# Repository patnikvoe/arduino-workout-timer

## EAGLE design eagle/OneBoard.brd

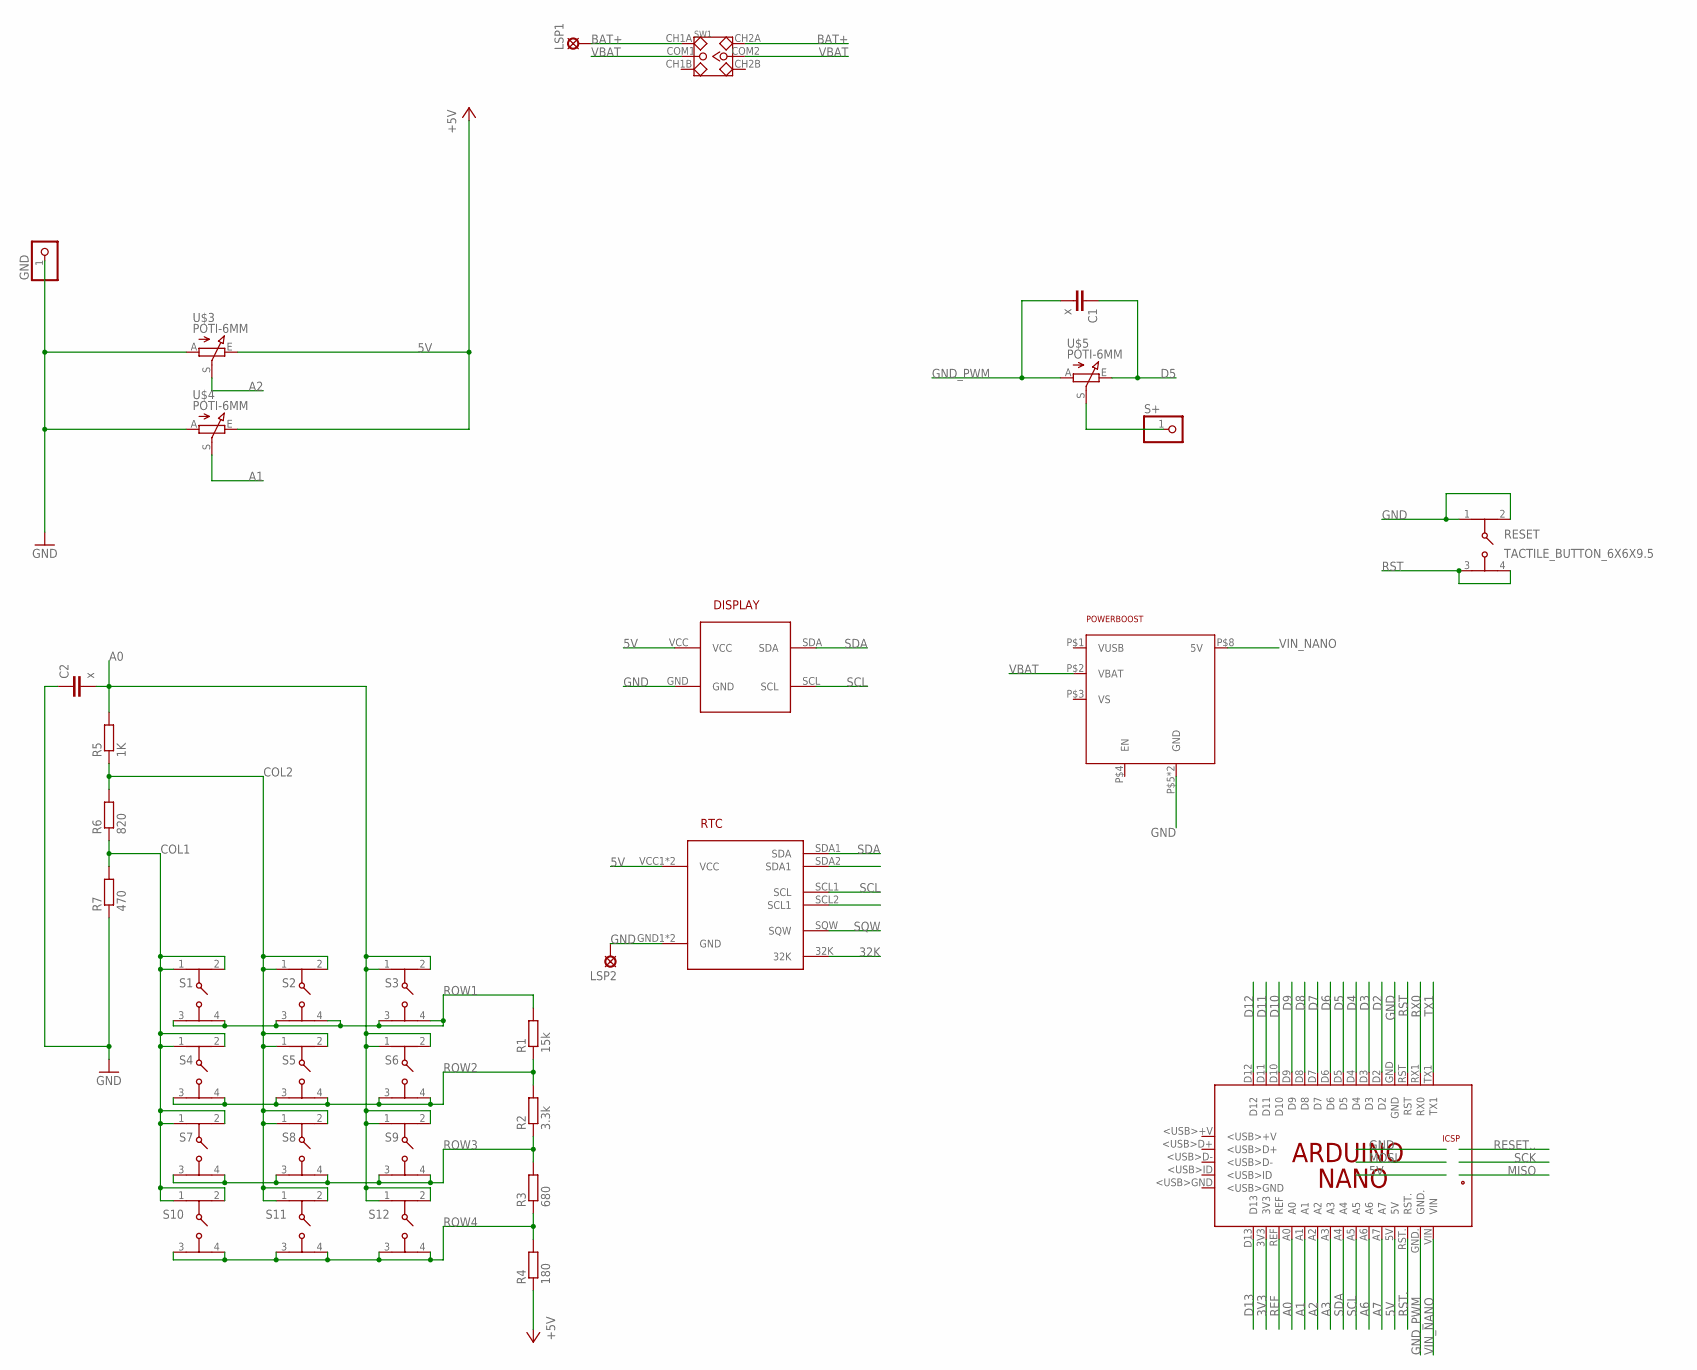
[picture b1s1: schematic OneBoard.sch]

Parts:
C1, C2: x; C025-025X050
DISPLAY: OLED_BREAKOUT; OLED_128X32_BREAKOUT
GND: PINHD-1X1; 1X01
LSP1, LSP2: LSP11
POWERBOOST: ADAFRUIT_POWERBOOST_1000C
R1: 15k; R0603
R2: 3.3k; R0603
R3: 680; R0603
R4: 180; R0603
R5: 1K; R0603
R6: 820; R0603
R7: 470; R0603
RESET: TACTILE_BUTTON_6X6X9.5; TACTILE_SWITCH_PTH_6.0MM
RTC: DS3231_BREAKOUT
S1, S2, S3, S4, S5, S6, S7, S8, S9, S10, S11, S12: TACTILE_BUTTON_6X6X9.5; TACTILE_SWITCH_PTH_6.0MM
S+: PINHD-1X1; 1X01
SW1: DIP-TOGGLE-SWITCH-2CH-(2X3P-2.54); SW6-2.54-9.0X3.5X3.2+2.0MM
U$3, U$4, U$5: POTI-6MM
U$7: ARDUINO-NANO; ARDUINO_NANO

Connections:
3V3: U$7.3V3
5V: DISPLAY.VCC, R4.1, RTC.VCC1 (VCC), RTC.VCC2 (VCC), U$3.E, U$4.E, U$7.5V, U$7.5V.
32K: RTC.32K
A0: C2.2, R5.2, S3.1, S3.2 (3), S6.1, S6.2 (3), S9.1, S9.2 (3), S12.1, S12.2 (3), U$7.A0
A1: U$4.S, U$7.A1
A2: U$3.S, U$7.A2
A3: U$7.A3
A6: U$7.A6
A7: U$7.A7
BAT+: LSP1.MP, SW1.CH1A, SW1.CH2A
COL1: R6.1, R7.2, S1.1, S1.2 (3), S4.1, S4.2 (3), S7.1, S7.2 (3), S10.1, S10.2 (3)
COL2: R5.1, R6.2, S2.1, S2.2 (3), S5.1, S5.2 (3), S8.1, S8.2 (3), S11.1, S11.2 (3)
D2: U$7.D2
D3: U$7.D3
D4: U$7.D4
D5: C1.1, U$5.E, U$7.D5
D6: U$7.D6
D7: U$7.D7
D8: U$7.D8
D9: U$7.D9
D10: U$7.D10
D11: U$7.D11
D12: U$7.D12
D13: U$7.D13
GND: C2.1, DISPLAY.GND, GND.1, LSP2.MP, POWERBOOST.P$5 (GND), POWERBOOST.P$7 (GND), R7.1, RESET.1, RESET.2 (3), RTC.GND1 (GND), RTC.GND2 (GND), U$3.A, U$4.A, U$7.GND, U$7.GND_
GND_PWM: C1.2, U$5.A, U$7.GND.
MISO: U$7.MISO
MOSI: U$7.MOSI
REF: U$7.REF
RESET..: U$7.RESET..
ROW1: R1.2, S1.3 (2), S1.4, S2.3 (2), S2.4, S3.3 (2), S3.4
ROW2: R1.1, R2.2, S4.3 (2), S4.4, S5.3 (2), S5.4, S6.3 (2), S6.4
ROW3: R2.1, R3.2, S7.3 (2), S7.4, S8.3 (2), S8.4, S9.3 (2), S9.4
ROW4: R3.1, R4.2, S10.3 (2), S10.4, S11.3 (2), S11.4, S12.3 (2), S12.4
RST: RESET.3 (2), RESET.4, U$7.RST
RST.: U$7.RST.
RX0: U$7.RX1 (RX0)
S+: S+.1, U$5.S
SCK: U$7.SCK
SCL: DISPLAY.SCL, RTC.SCL1 (SCL), U$7.A5
SDA: DISPLAY.SDA, RTC.SDA1 (SDA), U$7.A4
SQW: RTC.SQW
TX1: U$7.TX1
VBAT: POWERBOOST.P$2 (VBAT), SW1.COM1, SW1.COM2
VIN_NANO: POWERBOOST.P$8 (5V), U$7.VIN
VS: POWERBOOST.P$3 (VS)
VUSB: POWERBOOST.P$1 (VUSB)

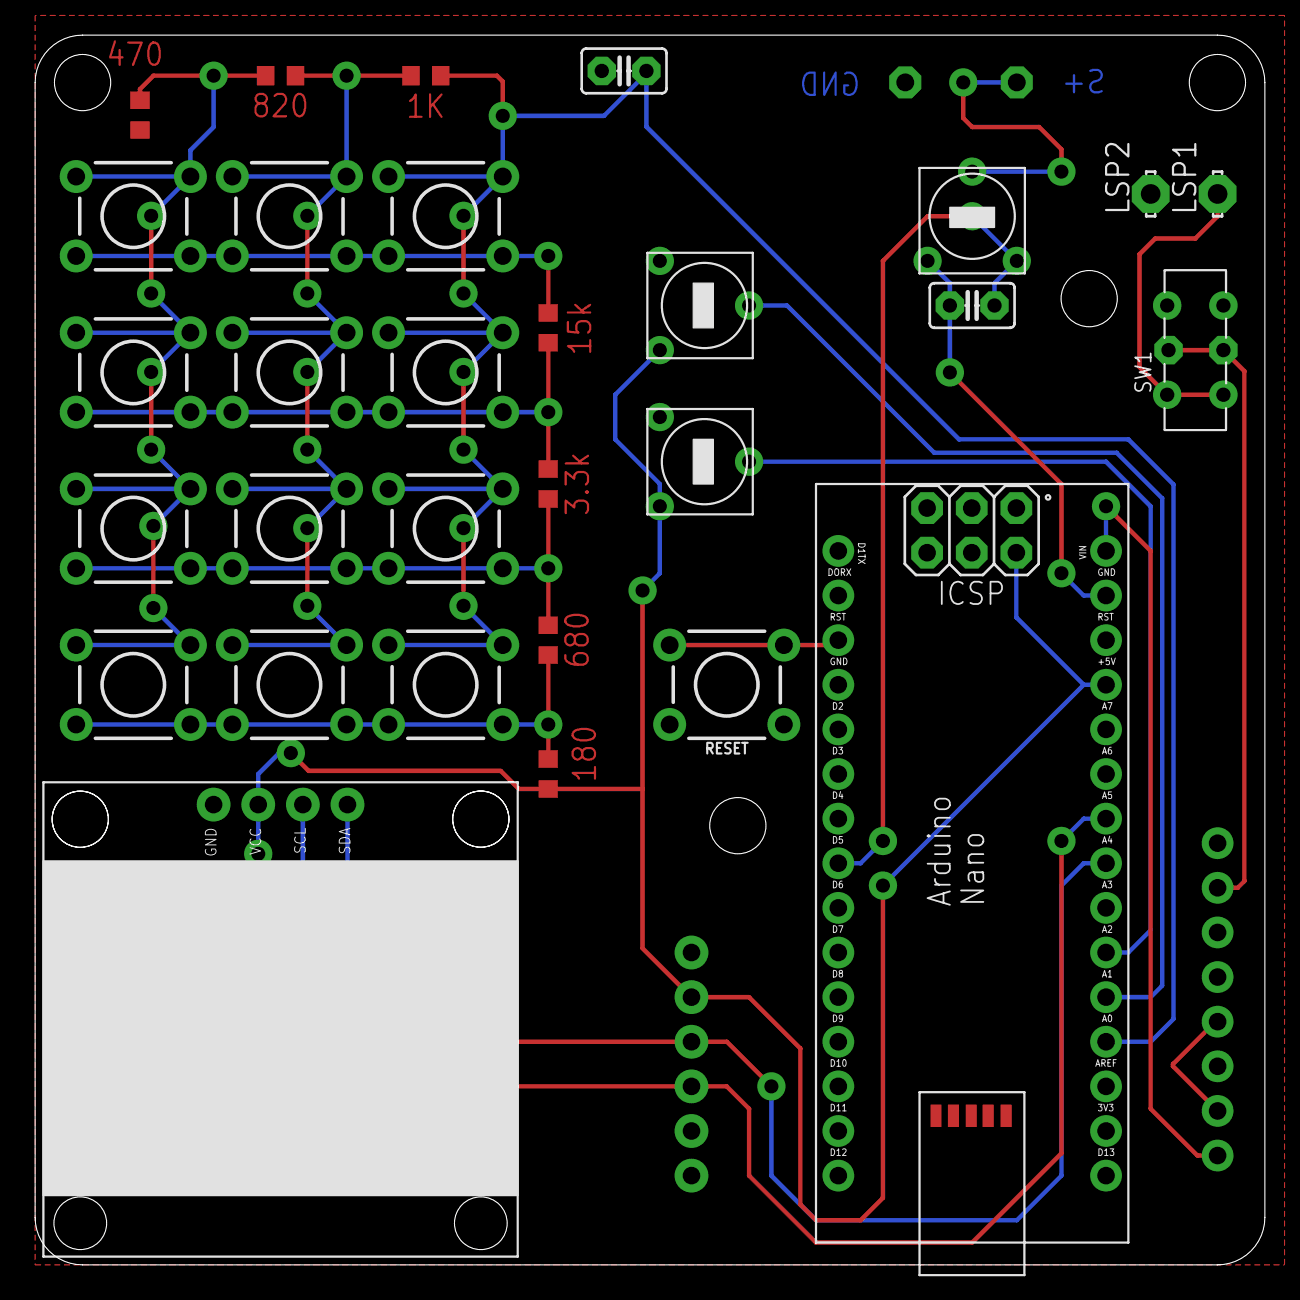
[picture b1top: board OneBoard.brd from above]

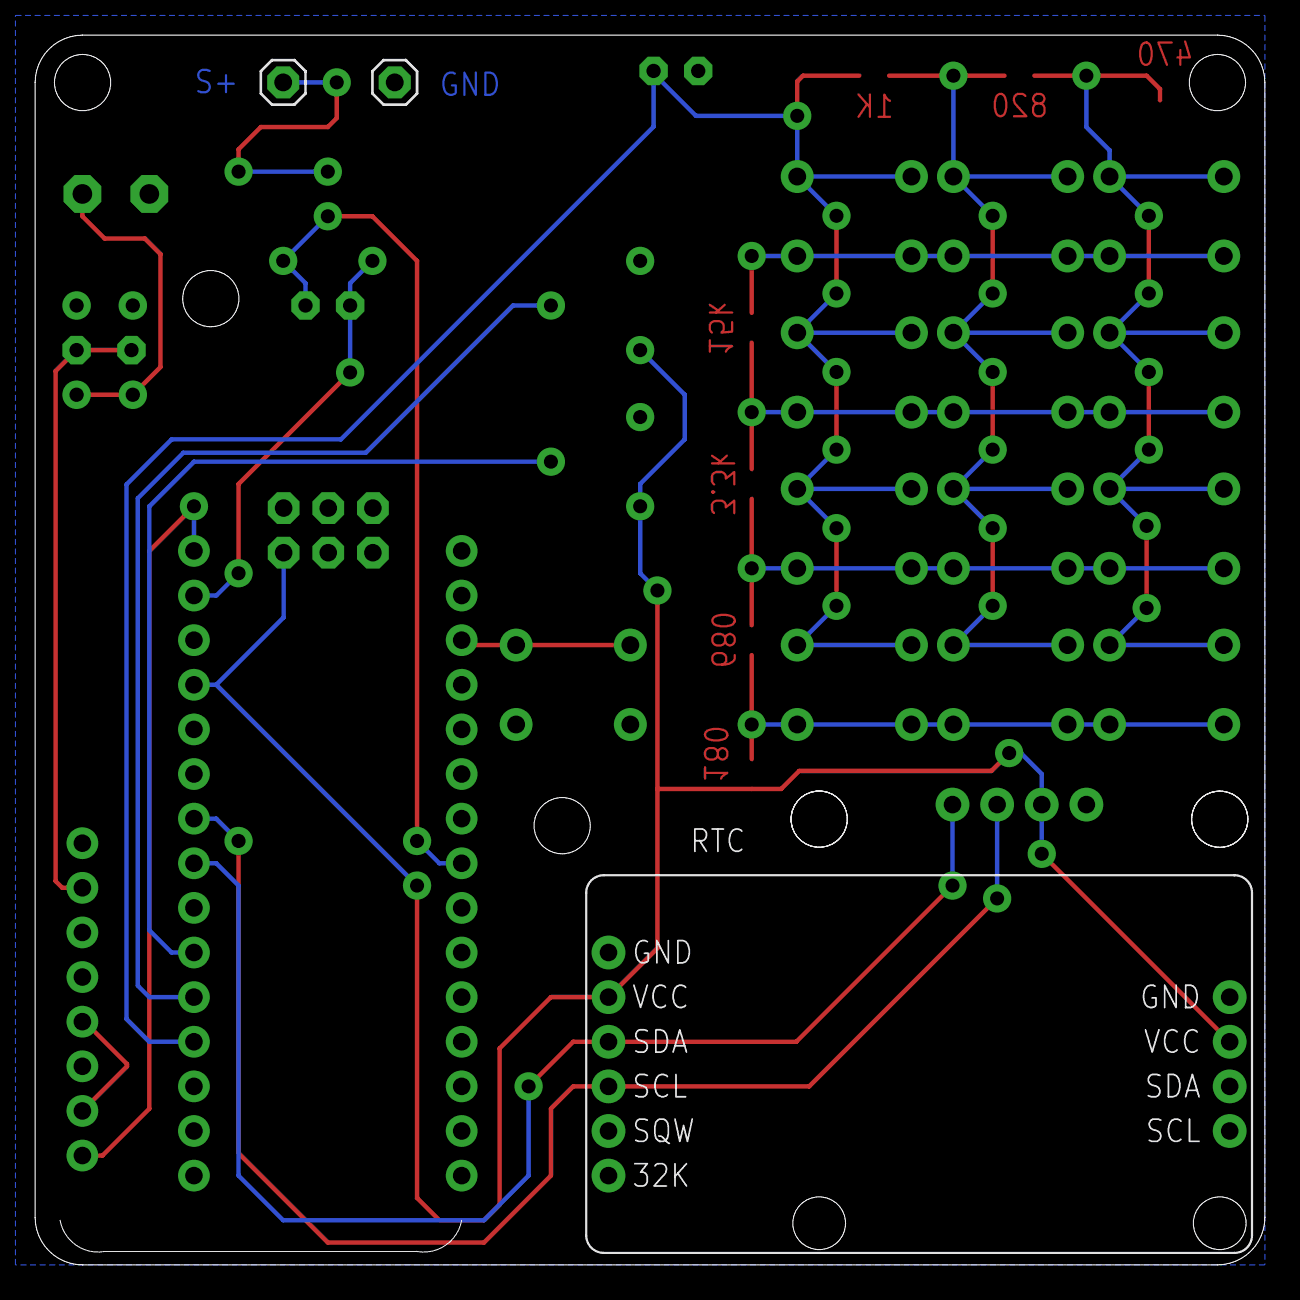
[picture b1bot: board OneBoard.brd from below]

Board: 2 copper layers, 70.0 x 70.0 mm, 34 parts (4 on the bottom side), 20 nets.

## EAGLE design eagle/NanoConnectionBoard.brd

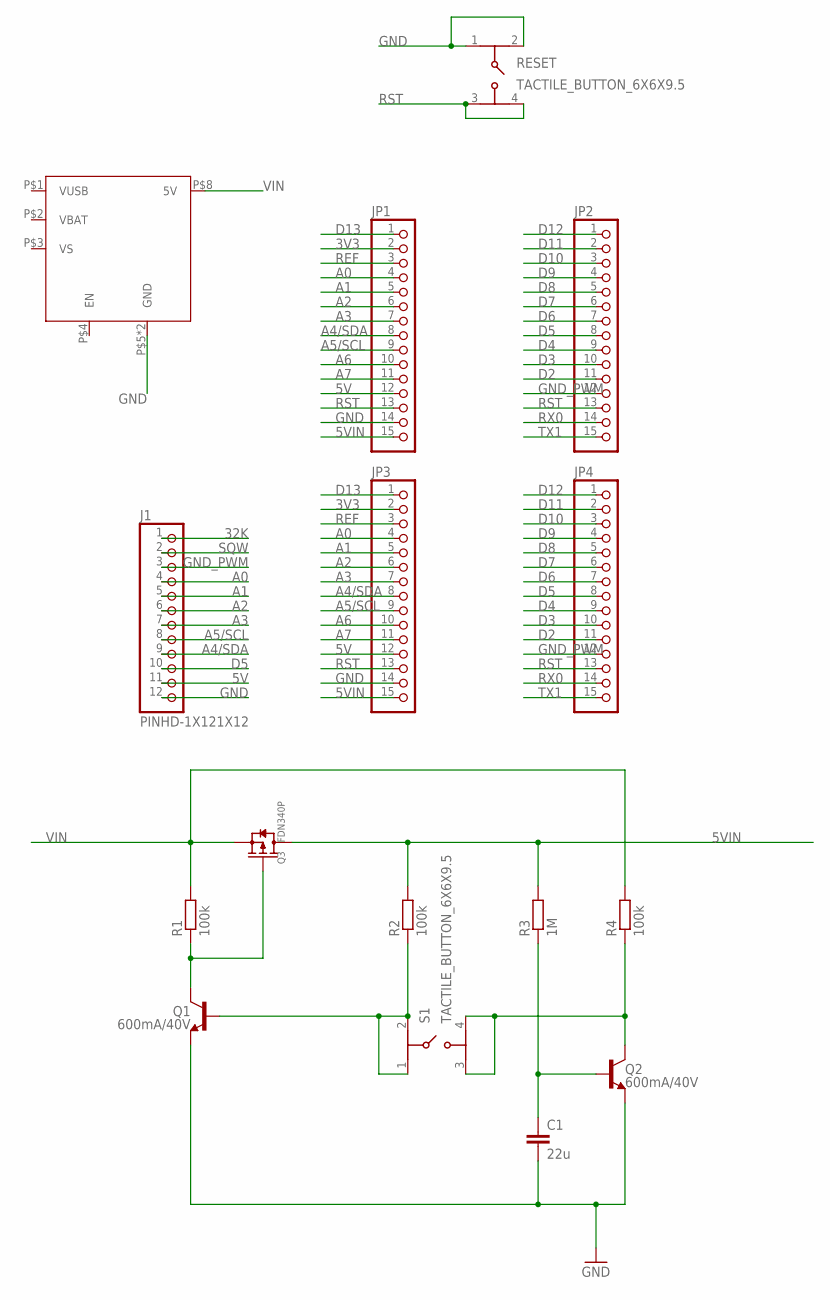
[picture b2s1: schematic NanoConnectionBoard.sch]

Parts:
C1: 22u; C1210K
J1: PINHD-1X121X12; 1X12
JP1, JP2, JP3, JP4: PINHD-1X15-CB; 1X15-CB
Q1, Q2: 600mA/40V; TO-92
Q3: FDN340P; SOT-23
R1, R2, R4: 100k; R0603
R3: 1M; R0603
RESET: TACTILE_BUTTON_6X6X9.5; TACTILE_SWITCH_PTH_6.0MM
S1: TACTILE_BUTTON_6X6X9.5; TACTILE_SWITCH_PTH_6.0MM
U$1: ADAFRUIT_POWERBOOST_1000C

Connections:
3V3: JP1.2, JP3.2
5V: J1.11, JP1.12, JP3.12
5VIN: JP1.15, JP3.15, Q3.3 (D), R2.2, R3.2
32K: J1.1
A0: J1.4, JP1.4, JP3.4
A1: J1.5, JP1.5, JP3.5
A2: J1.6, JP1.6, JP3.6
A3: J1.7, JP1.7, JP3.7
A4/SDA: J1.9, JP1.8, JP3.8
A5/SCL: J1.8, JP1.9, JP3.9
A6: JP1.10, JP3.10
A7: JP1.11, JP3.11
D2: JP2.11, JP4.11
D3: JP2.10, JP4.10
D4: JP2.9, JP4.9
D5: J1.10, JP2.8, JP4.8
D6: JP2.7, JP4.7
D7: JP2.6, JP4.6
D8: JP2.5, JP4.5
D9: JP2.4, JP4.4
D10: JP2.3, JP4.3
D11: JP2.2, JP4.2
D12: JP2.1, JP4.1
D13: JP1.1, JP3.1
GND: C1.2, J1.12, JP1.14, JP3.14, Q1.3 (E), Q2.3 (E), RESET.1, RESET.2 (3), U$1.P$5 (GND), U$1.P$7 (GND)
GND_PWM: J1.3, JP2.12, JP4.12
unnamed: C1.1, Q2.2 (B), R3.1
unnamed: Q2.1 (C), R4.1, S1.3 (2), S1.4
unnamed: Q1.1 (C), Q3.1 (G), R1.1
unnamed: Q1.2 (B), R2.1, S1.1, S1.2 (3)
REF: JP1.3, JP3.3
RST: JP1.13, JP2.13, JP3.13, JP4.13, RESET.3 (2), RESET.4
RX0: JP2.14, JP4.14
SQW: J1.2
TX1: JP2.15, JP4.15
VBAT: U$1.P$2 (VBAT)
VIN: Q3.2 (S), R1.2, R4.2, U$1.P$8 (5V)
VS: U$1.P$3 (VS)
VUSB: U$1.P$1 (VUSB)

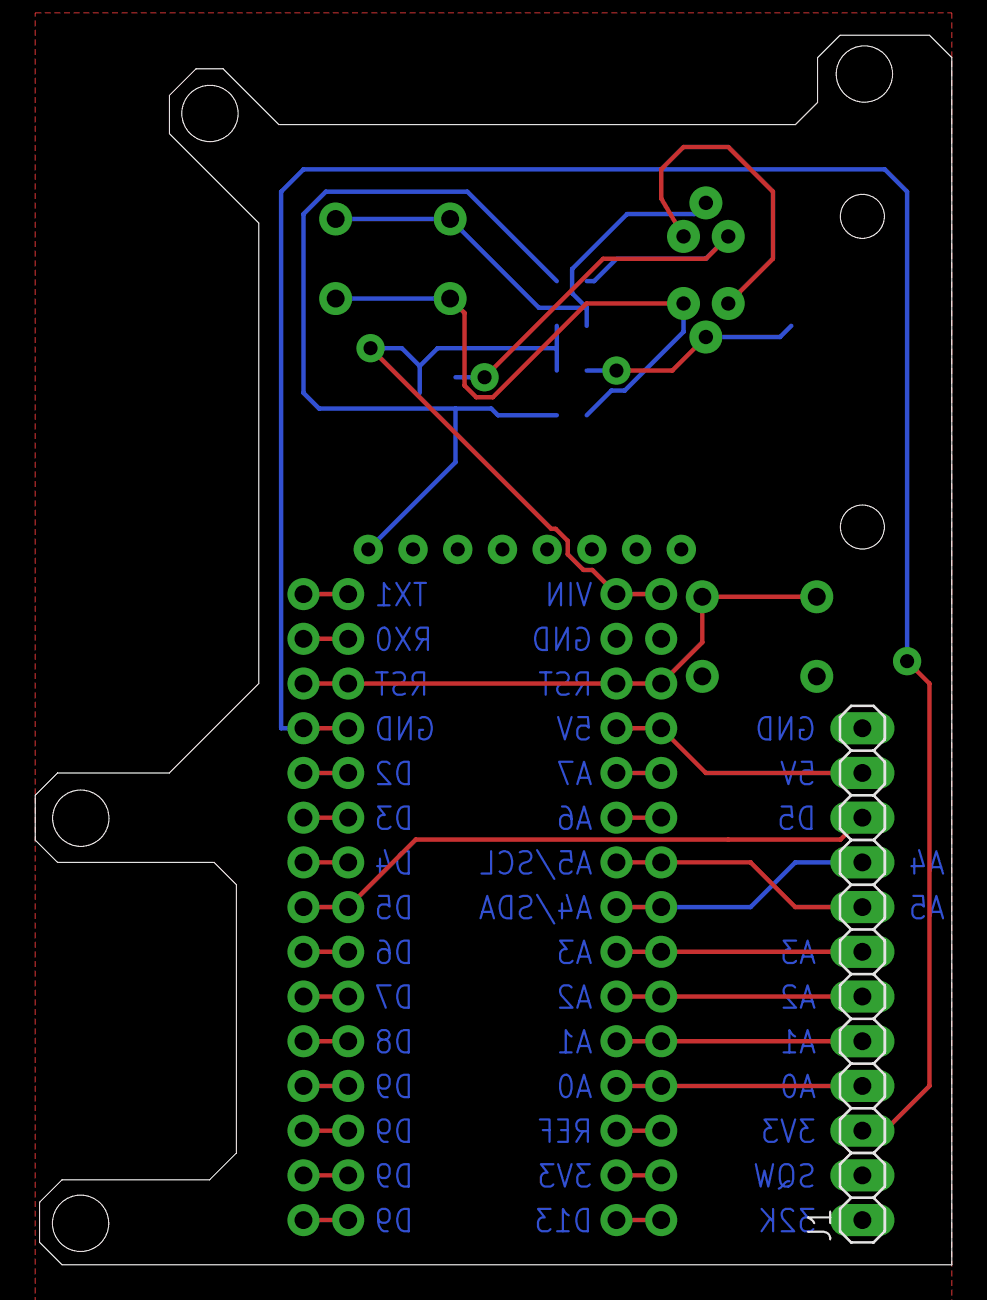
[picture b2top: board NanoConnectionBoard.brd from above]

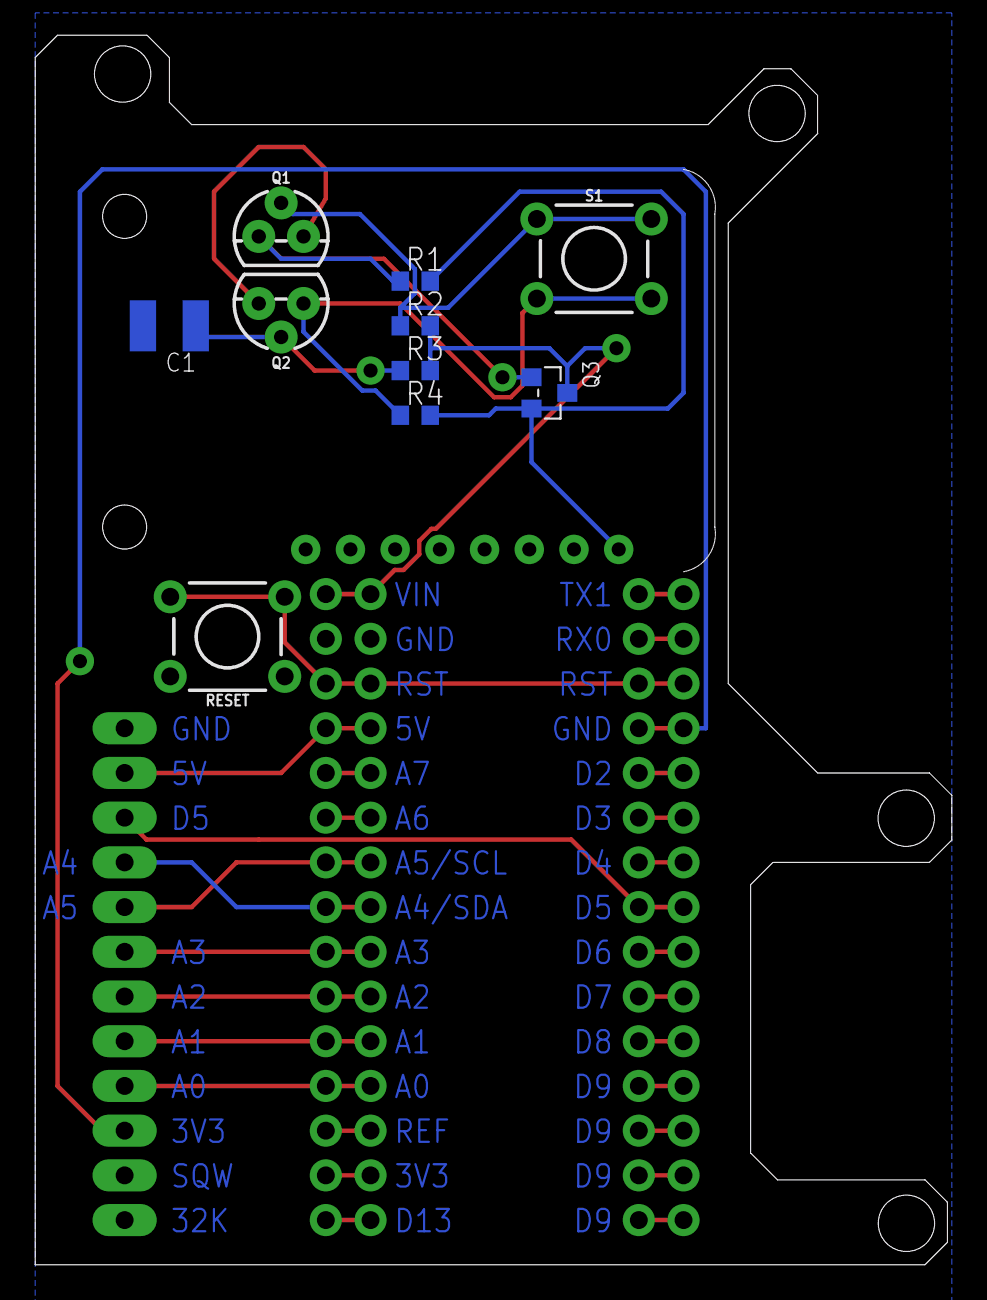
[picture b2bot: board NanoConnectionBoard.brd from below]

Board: 2 copper layers, 52.1 x 69.8 mm, 16 parts (13 on the bottom side), 34 nets.

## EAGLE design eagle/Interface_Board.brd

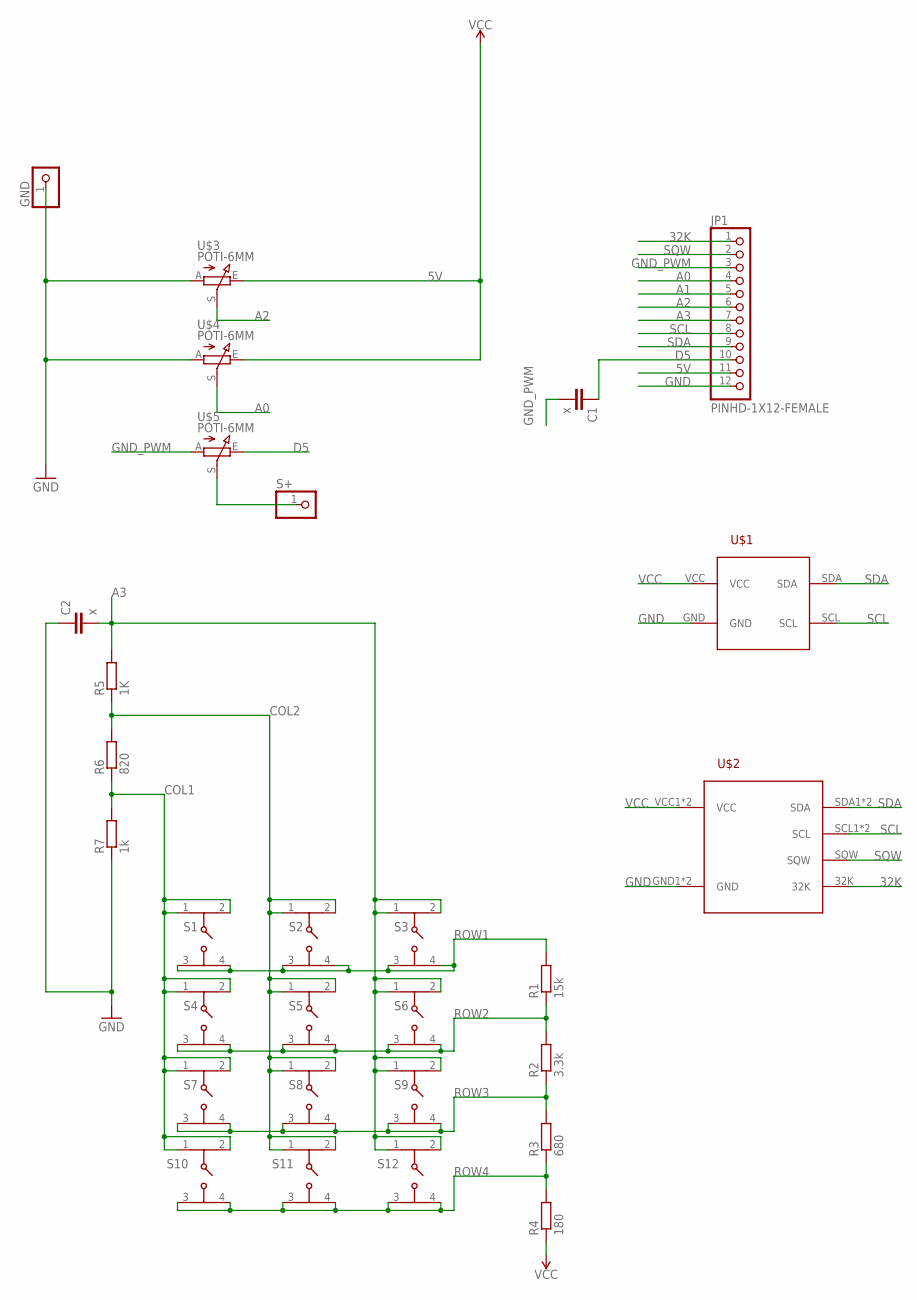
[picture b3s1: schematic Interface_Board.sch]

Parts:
C1, C2: x; C025-025X050
GND: PINHD-1X1; 1X01
JP1: PINHD-1X12-FEMALE; 1X12-FEMALE
R1: 15k; R0603
R2: 3.3k; R0603
R3: 680; R0603
R4: 180; R0603
R5: 1K; R0603
R6: 820; R0603
R7: 1k; R0603
S1, S2, S3, S4, S5, S6, S7, S8, S9, S10, S11, S12: TACTILE_BUTTON_6X6X9.5; TACTILE_SWITCH_PTH_6.0MM
S+: PINHD-1X1; 1X01
U$1: OLED_BREAKOUT; OLED_128X32_BREAKOUT
U$2: DS3231_BREAKOUT
U$3, U$4, U$5: POTI-6MM

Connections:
5V: JP1.11, U$3.E, U$4.E
32K: JP1.1, U$2.32K
A0: JP1.4, U$4.S
A1: JP1.5
A2: JP1.6, U$3.S
A3: C2.2, JP1.7, R5.2, S3.1, S3.2 (3), S6.1, S6.2 (3), S9.1, S9.2 (3), S12.1, S12.2 (3)
COL1: R6.1, R7.2, S1.1, S1.2 (3), S4.1, S4.2 (3), S7.1, S7.2 (3), S10.1, S10.2 (3)
COL2: R5.1, R6.2, S2.1, S2.2 (3), S5.1, S5.2 (3), S8.1, S8.2 (3), S11.1, S11.2 (3)
D5: C1.1, JP1.10, U$5.E
GND: C2.1, GND.1, JP1.12, R7.1, U$1.GND, U$2.GND1 (GND), U$2.GND2 (GND), U$3.A, U$4.A
GND_PWM: C1.2, JP1.3, U$5.A
ROW1: R1.2, S1.3 (2), S1.4, S2.3 (2), S2.4, S3.3 (2), S3.4
ROW2: R1.1, R2.2, S4.3 (2), S4.4, S5.3 (2), S5.4, S6.3 (2), S6.4
ROW3: R2.1, R3.2, S7.3 (2), S7.4, S8.3 (2), S8.4, S9.3 (2), S9.4
ROW4: R3.1, R4.2, S10.3 (2), S10.4, S11.3 (2), S11.4, S12.3 (2), S12.4
S+: S+.1, U$5.S
SCL: JP1.8, U$1.SCL, U$2.SCL1 (SCL), U$2.SCL2 (SCL)
SDA: JP1.9, U$1.SDA, U$2.SDA1 (SDA), U$2.SDA2 (SDA)
SQW: JP1.2, U$2.SQW
VCC: R4.1, U$1.VCC, U$2.VCC1 (VCC), U$2.VCC2 (VCC)

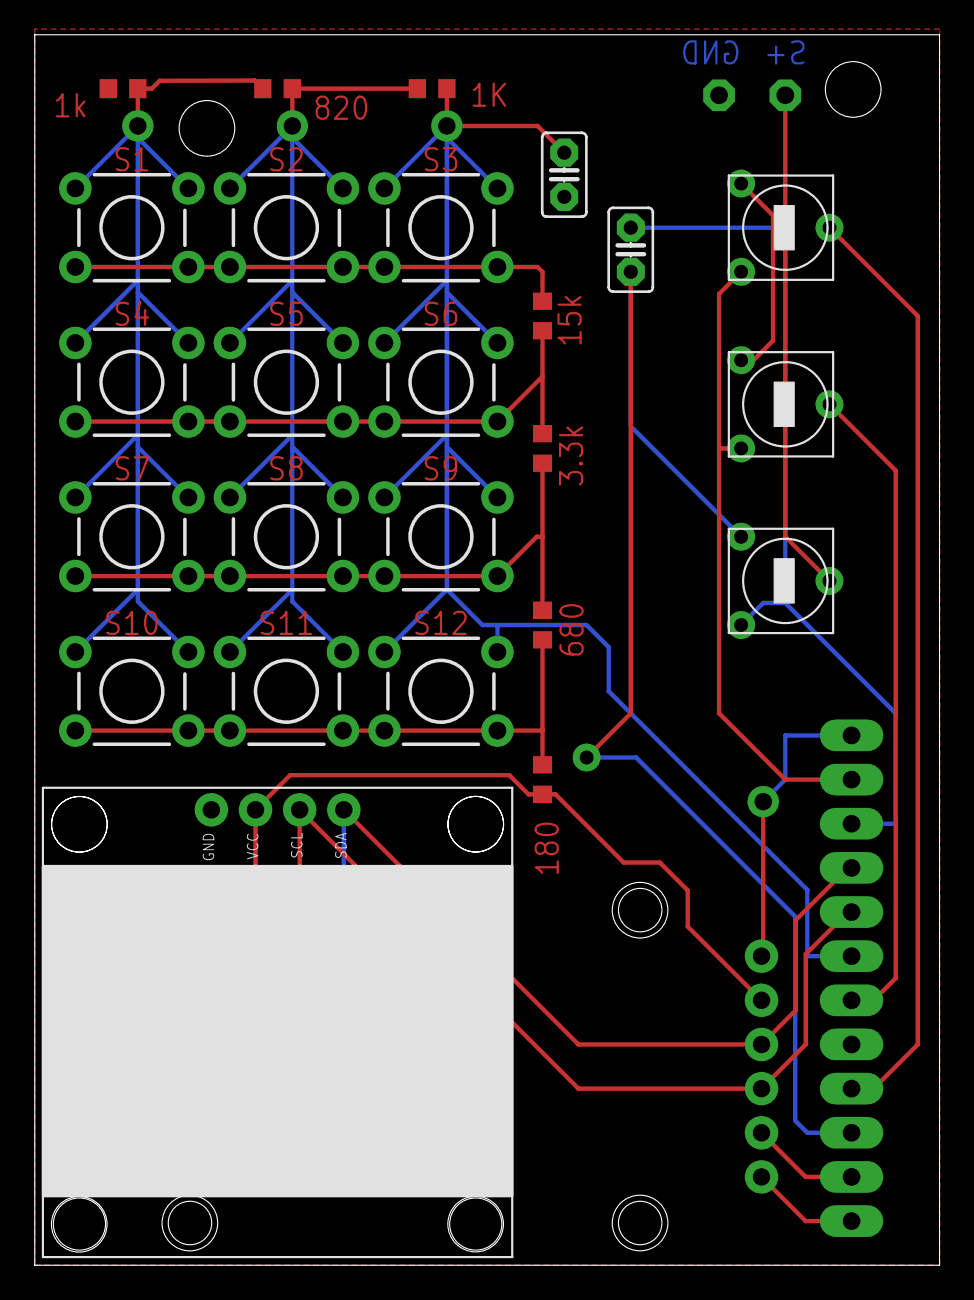
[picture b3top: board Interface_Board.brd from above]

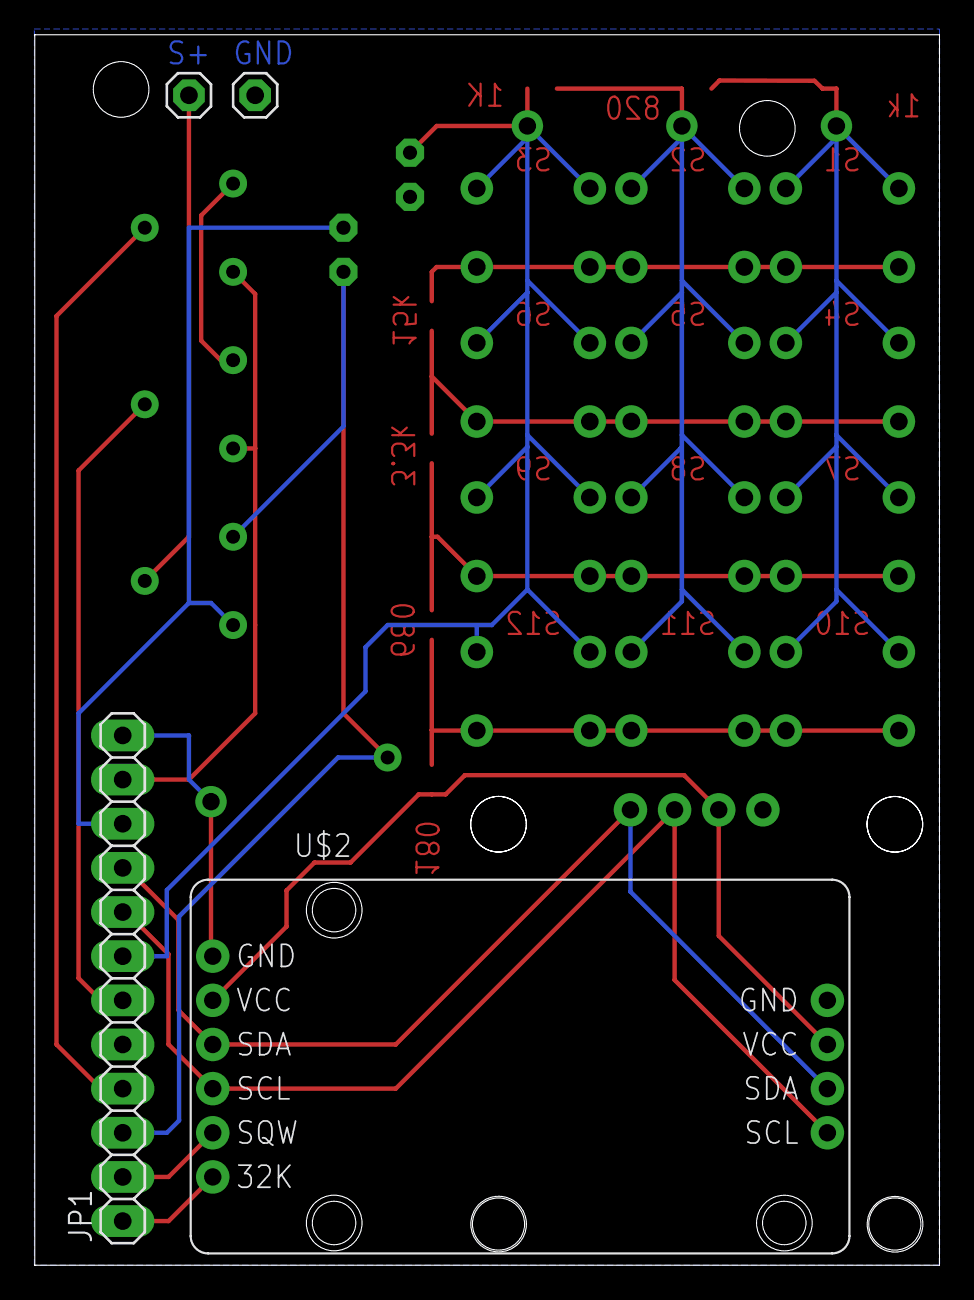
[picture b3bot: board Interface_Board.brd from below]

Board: 2 copper layers, 52.0 x 70.8 mm, 29 parts (4 on the bottom side), 19 nets.

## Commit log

2018-05-29 New CAM output
2018-05-29 Adjusted Boardlayout and Schematic
2018-05-29 eagle project update
2018-05-29 Arduino code updated

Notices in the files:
parts and their libraries:
SparkFun-PowerSymbols: Licensing: Creative Commons ShareAlike 4.0 International - https://creativecommons.org/licenses/by-sa/4.0
